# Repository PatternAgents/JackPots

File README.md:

# JackPots { ERA : Four (4) Attenuator, Eight (8) Jack board }

Format : ERA / Eurorack / Breadboard Friendly

Height : 1U 

Width: 16HP

Depth : 1.0 cm

Power : +12V 20mA

Jacks : 3.5mm mono (Thonkicon)

JackPots is a simple quad Attenuator I/O module.

[JackPots](https://github.com/patternagents/JackPots)

JackPots can be used on a breadboard for prototyping new circuits,
or it can mounted into a 1U Rack system using the following 1U x 16 HP front panel design.

[JackPots 1U Front Panel](https://github.com/patternagents/JackPots)

JackPots can be used in combination with two (2) or more other ERA modules
for mounting in a 3U ERA or Eurorack format card or even larger rack format

---------------------------------------

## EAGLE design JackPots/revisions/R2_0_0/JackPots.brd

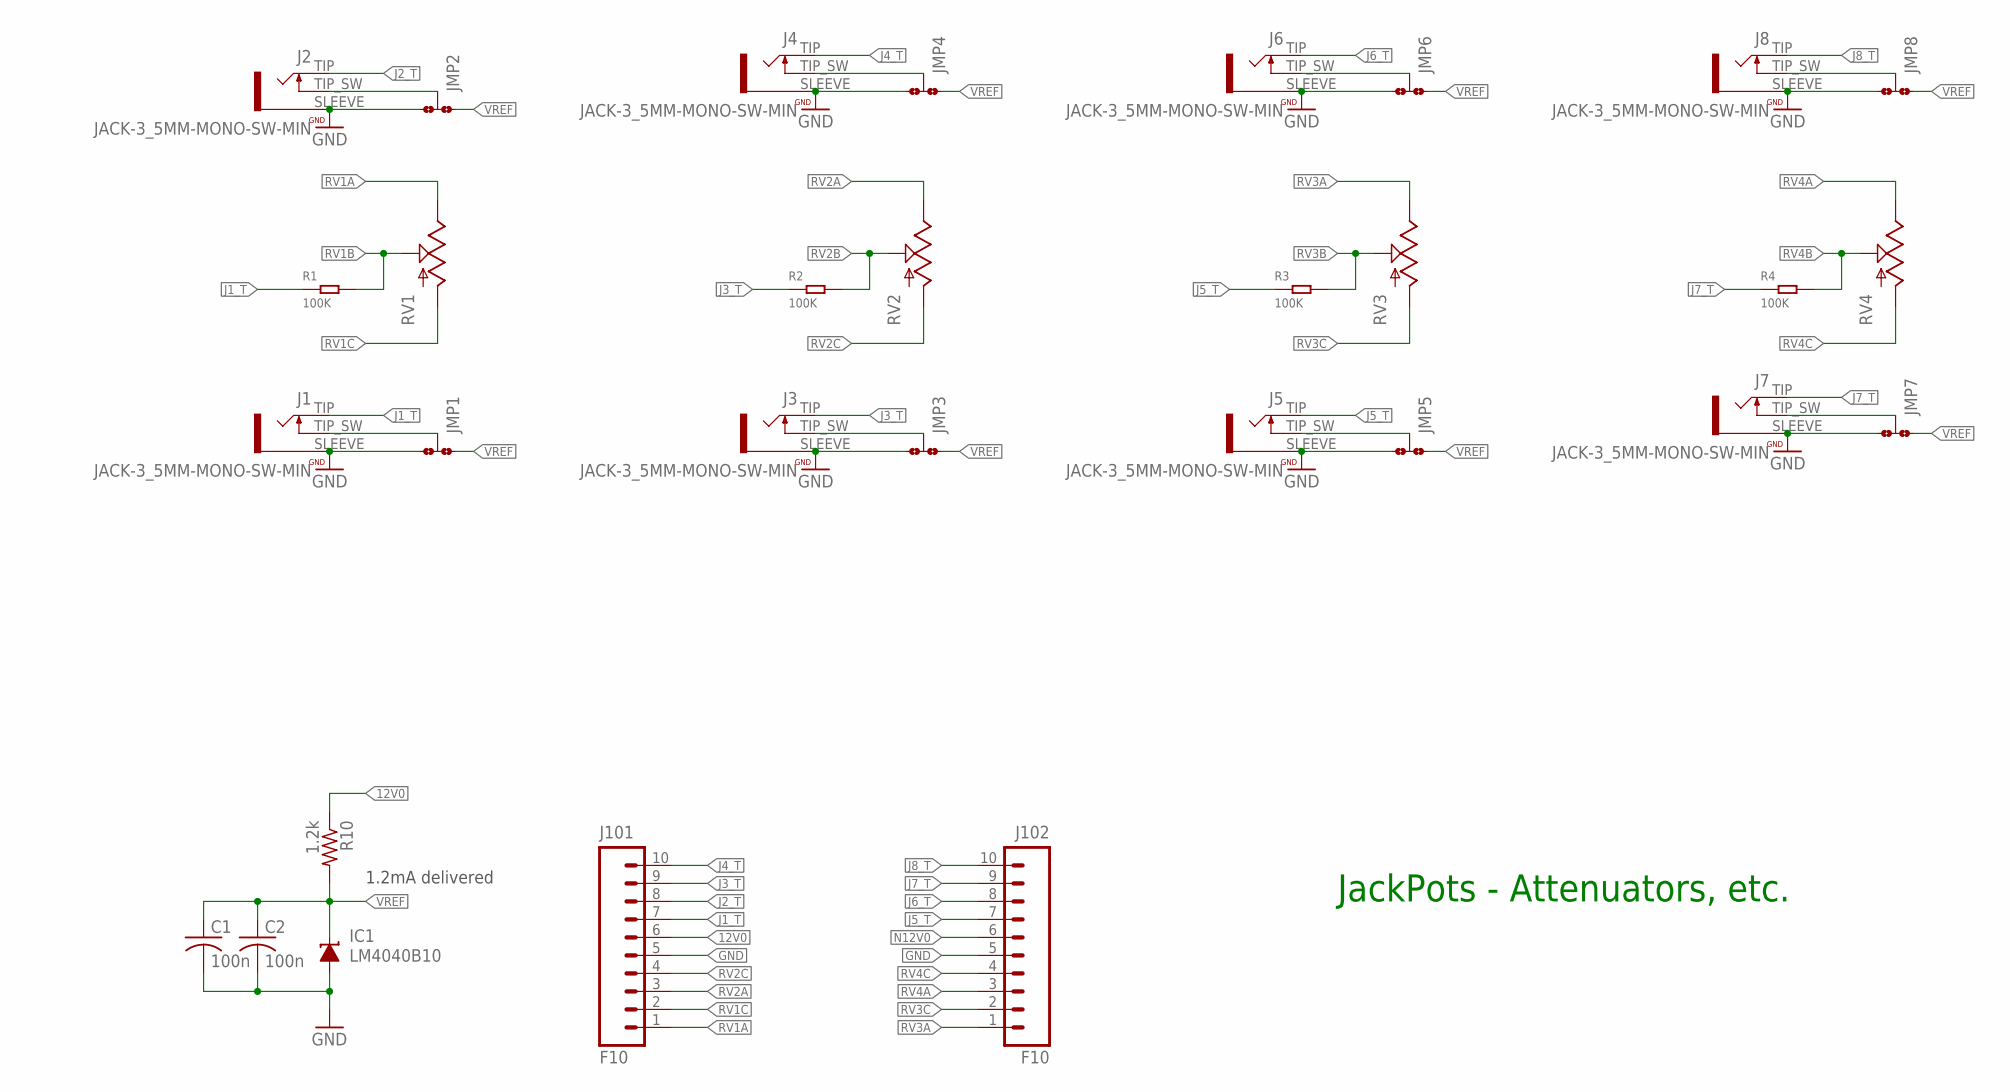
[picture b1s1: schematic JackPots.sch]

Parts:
C1, C2: 100n; C0603
IC1: LM4040B10; DBZ_R-PDSO-G3
J1, J2, J3, J4, J5, J6, J7, J8: JACK-3_5MM-MONO-SW-MIN; WQP_PJ301M-MIN
J101, J102: F10; 1X10_OCTO
JMP1, JMP2, JMP3, JMP4, JMP5, JMP6, JMP7, JMP8: JMP-3-NO-0603
R1, R2, R3, R4: 100K; R0603
R10: 1.2k; R0603
RV1, RV2, RV3, RV4: POT; ALPS_POT

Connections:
12V0: J101.6, R10.1
GND: C1.2, C2.2, IC1.2 (A), J1.SLEEVE, J2.SLEEVE, J3.SLEEVE, J4.SLEEVE, J5.SLEEVE, J6.SLEEVE, J7.SLEEVE, J8.SLEEVE, J101.5, J102.5, JMP1.3, JMP2.3, JMP3.3, JMP4.3, JMP5.3, JMP6.3, JMP7.3, JMP8.3
J1_T: J1.TIP, J101.7, R1.1
J1_TN: J1.TIP_SW, JMP1.2
J2_T: J2.TIP, J101.8
J2_TN: J2.TIP_SW, JMP2.2
J3_T: J3.TIP, J101.9, R2.1
J3_TN: J3.TIP_SW, JMP3.2
J4_T: J4.TIP, J101.10
J4_TN: J4.TIP_SW, JMP4.2
J5_T: J5.TIP, J102.7, R3.1
J5_TN: J5.TIP_SW, JMP5.2
J6_T: J6.TIP, J102.8
J6_TN: J6.TIP_SW, JMP6.2
J7_T: J7.TIP, J102.9, R4.1
J7_TN: J7.TIP_SW, JMP7.2
J8_T: J8.TIP, J102.10
J8_TN: J8.TIP_SW, JMP8.2
N12V0: J102.6
RV1A: J101.1, RV1.P$1 (3)
RV1B: R1.2, RV1.P$2 (2)
RV1C: J101.2, RV1.P$3 (1)
RV2A: J101.3, RV2.P$1 (3)
RV2B: R2.2, RV2.P$2 (2)
RV2C: J101.4, RV2.P$3 (1)
RV3A: J102.1, RV3.P$1 (3)
RV3B: R3.2, RV3.P$2 (2)
RV3C: J102.2, RV3.P$3 (1)
RV4A: J102.3, RV4.P$1 (3)
RV4B: R4.2, RV4.P$2 (2)
RV4C: J102.4, RV4.P$3 (1)
VREF: C1.1, C2.1, IC1.1 (C), JMP1.1, JMP2.1, JMP3.1, JMP4.1, JMP5.1, JMP6.1, JMP7.1, JMP8.1, R10.2

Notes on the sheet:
JackPots - Attenuators, etc.
1.2mA delivered

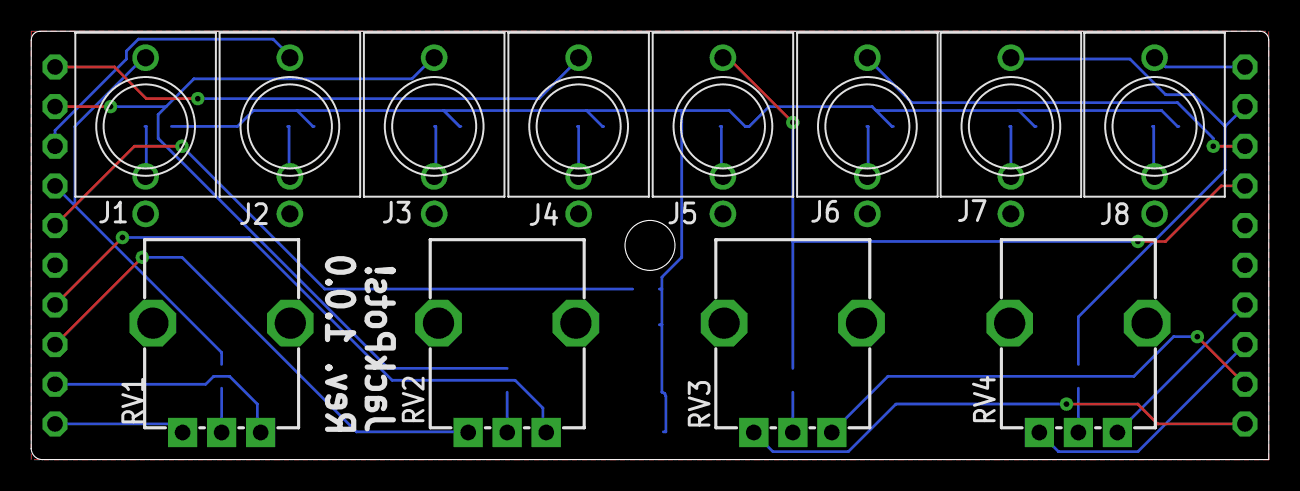
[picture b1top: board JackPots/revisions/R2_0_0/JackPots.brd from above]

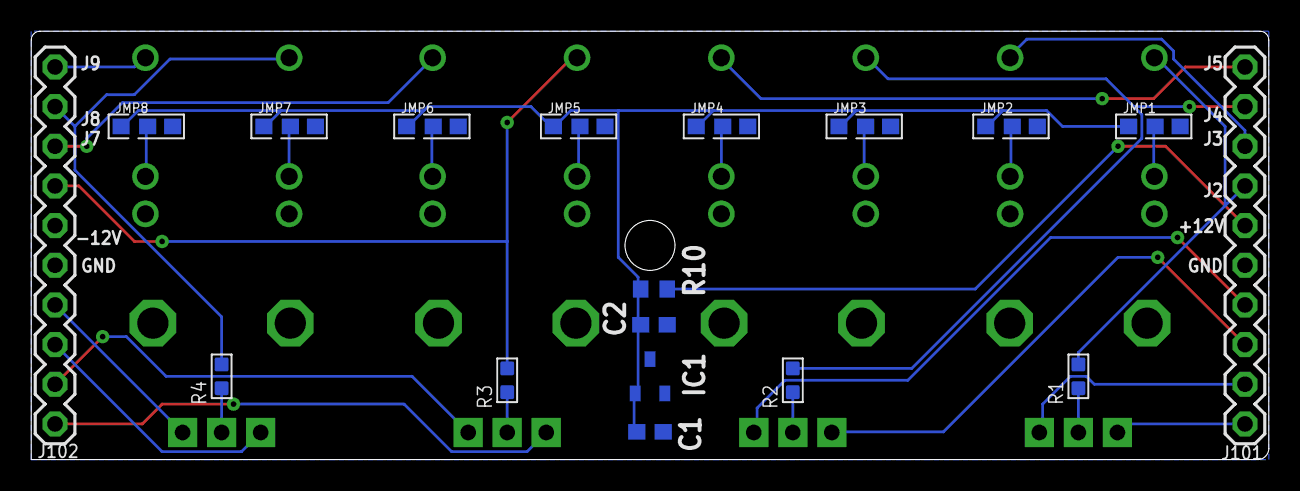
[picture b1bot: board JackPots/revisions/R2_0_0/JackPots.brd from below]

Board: 2 copper layers, 79.2 x 27.4 mm, 30 parts (18 on the bottom side), 31 nets.

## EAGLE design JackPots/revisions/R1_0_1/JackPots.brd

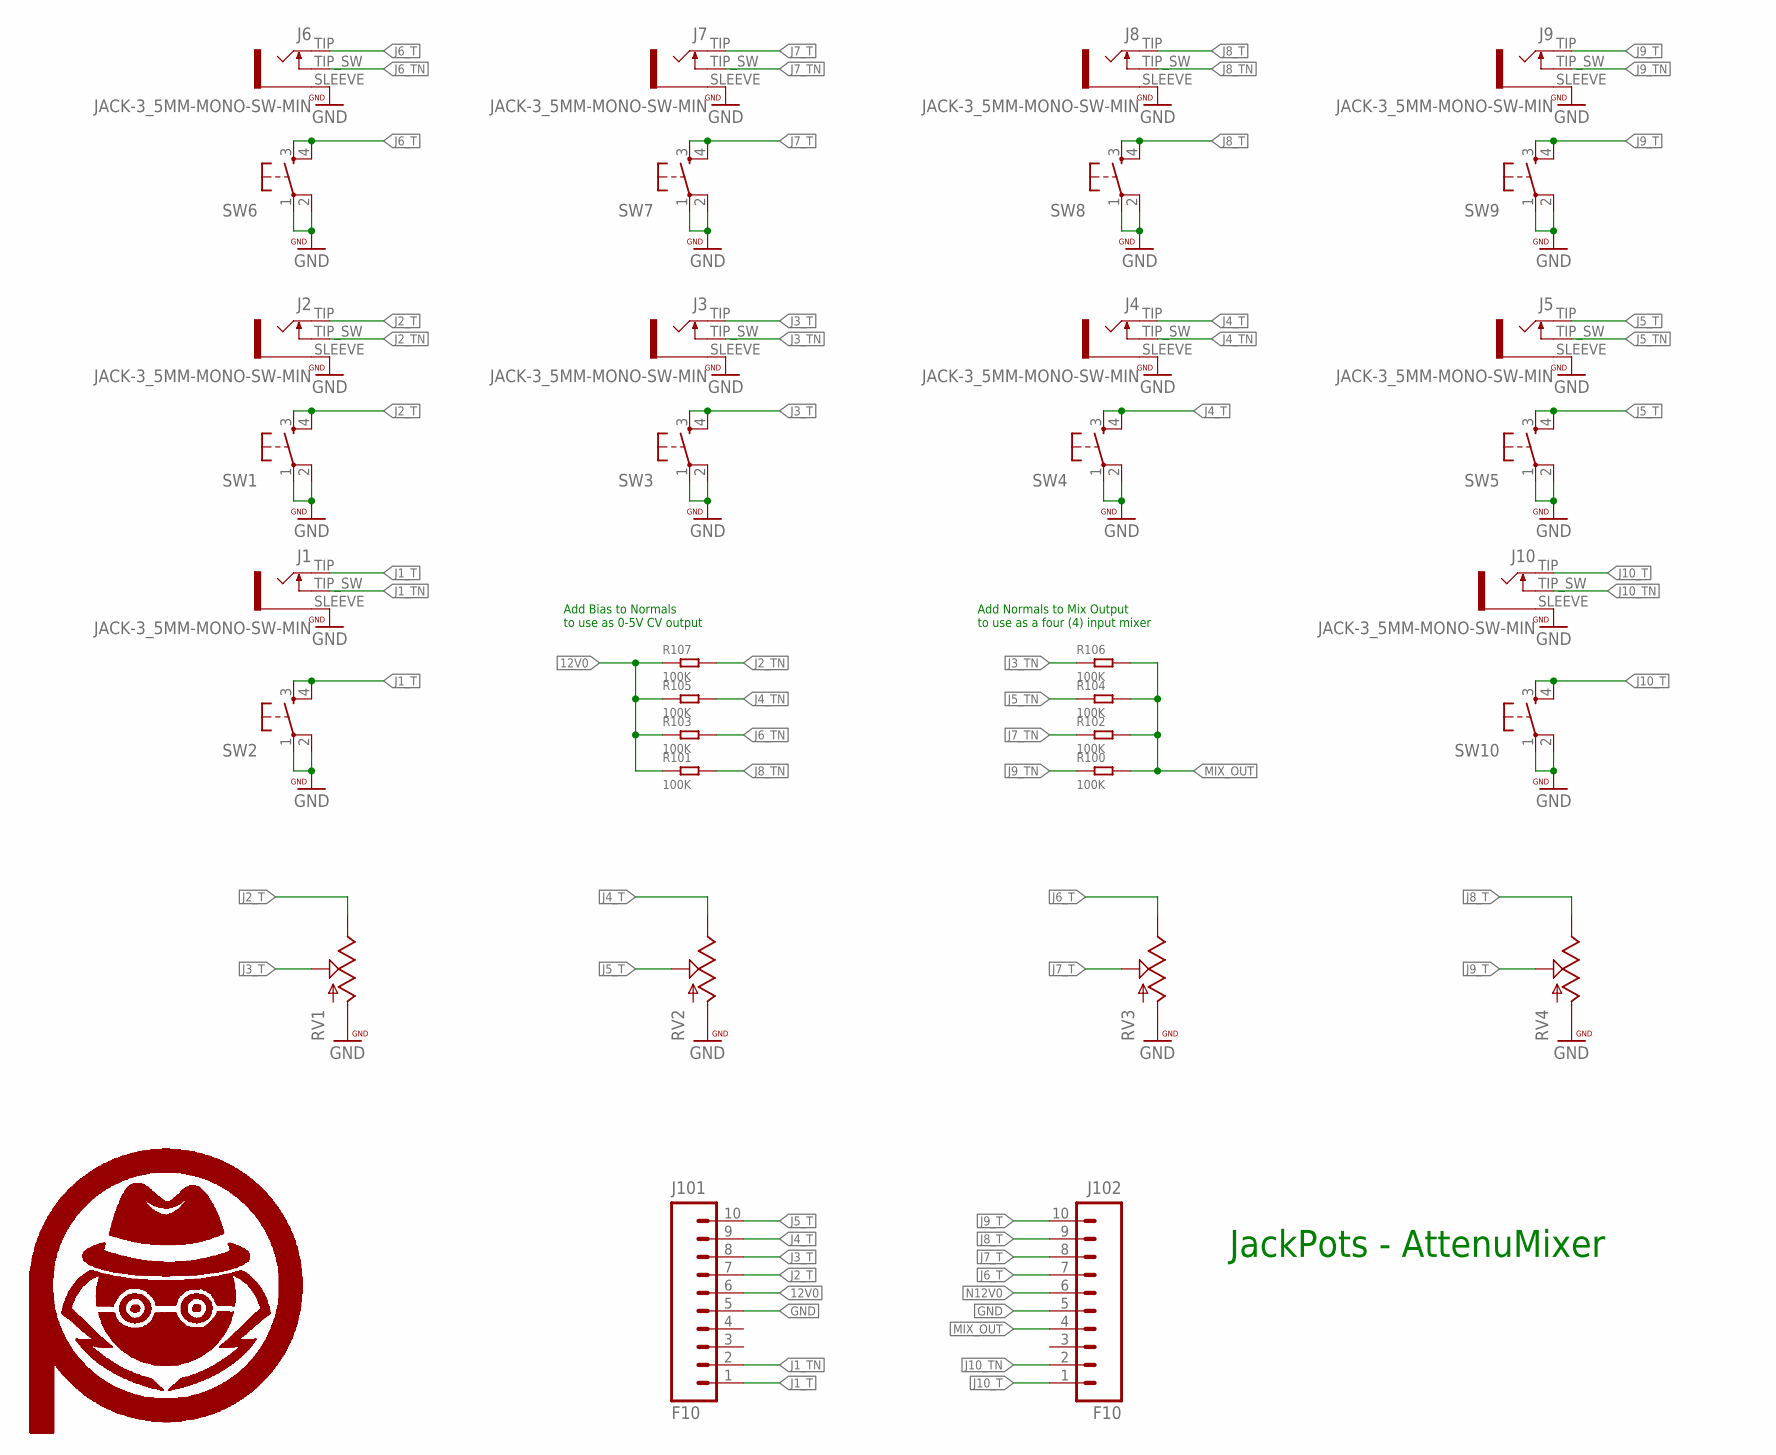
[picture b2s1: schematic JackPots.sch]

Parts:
$$U$1: PA_LOGO_SYMSMALL; PA_LOGO_AGENT_SMALL_SYM
$$U$100, $$U$101: PA_LOGO_SYMMED; PA_LOGO_AGENT_MED_SYM
J1, J2, J3, J4, J5, J6, J7, J8, J9, J10: JACK-3_5MM-MONO-SW-MIN; WQP_PJ301M-MIN
J101, J102: F10; 1X10_OCTO
R100, R101, R102, R103, R104, R105, R106, R107: 100K; R0603
RV1, RV2, RV3, RV4: POT; ALPS_POT
SW1, SW2, SW3, SW4, SW5, SW6, SW7, SW8, SW9, SW10: TAC_SWITCHPTH; TACTILE-PTH

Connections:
12V0: J101.6, R101.1, R103.1, R105.1, R107.1
GND: J1.SLEEVE, J2.SLEEVE, J3.SLEEVE, J4.SLEEVE, J5.SLEEVE, J6.SLEEVE, J7.SLEEVE, J8.SLEEVE, J9.SLEEVE, J10.SLEEVE, J101.5, J102.5, RV1.P$3 (1), RV2.P$3 (1), RV3.P$3 (1), RV4.P$3 (1), SW1.1, SW1.2, SW2.1, SW2.2, SW3.1, SW3.2, SW4.1, SW4.2, SW5.1, SW5.2, SW6.1, SW6.2, SW7.1, SW7.2, SW8.1, SW8.2, SW9.1, SW9.2, SW10.1, SW10.2
J1_T: J1.TIP, J101.1, SW2.3, SW2.4
J1_TN: J1.TIP_SW, J101.2
J2_T: J2.TIP, J101.7, RV1.P$1 (3), SW1.3, SW1.4
J2_TN: J2.TIP_SW, R107.2
J3_T: J3.TIP, J101.8, RV1.P$2 (2), SW3.3, SW3.4
J3_TN: J3.TIP_SW, R106.1
J4_T: J4.TIP, J101.9, RV2.P$1 (3), SW4.3, SW4.4
J4_TN: J4.TIP_SW, R105.2
J5_T: J5.TIP, J101.10, RV2.P$2 (2), SW5.3, SW5.4
J5_TN: J5.TIP_SW, R104.1
J6_T: J6.TIP, J102.7, RV3.P$1 (3), SW6.3, SW6.4
J6_TN: J6.TIP_SW, R103.2
J7_T: J7.TIP, J102.8, RV3.P$2 (2), SW7.3, SW7.4
J7_TN: J7.TIP_SW, R102.1
J8_T: J8.TIP, J102.9, RV4.P$1 (3), SW8.3, SW8.4
J8_TN: J8.TIP_SW, R101.2
J9_T: J9.TIP, J102.10, RV4.P$2 (2), SW9.3, SW9.4
J9_TN: J9.TIP_SW, R100.1
J10_T: J10.TIP, J102.1, SW10.3, SW10.4
J10_TN: J10.TIP_SW, J102.2
MIX_OUT: J102.4, R100.2, R102.2, R104.2, R106.2
N12V0: J102.6

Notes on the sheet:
Add Bias to Normals to use as 0-5V CV output
Add Normals to Mix Output to use as a four (4) input mixer
JackPots - AttenuMixer

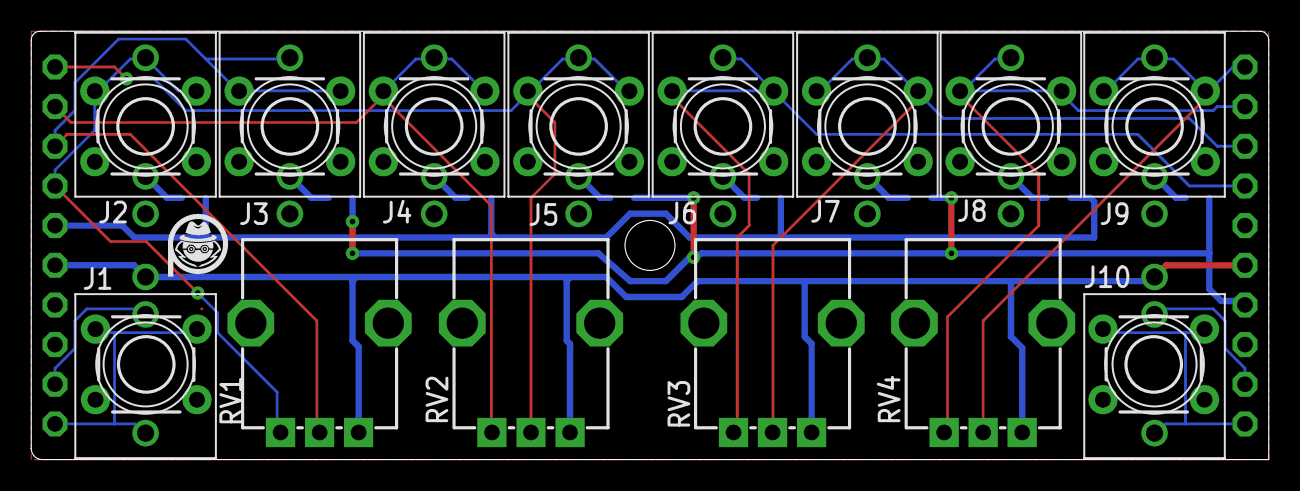
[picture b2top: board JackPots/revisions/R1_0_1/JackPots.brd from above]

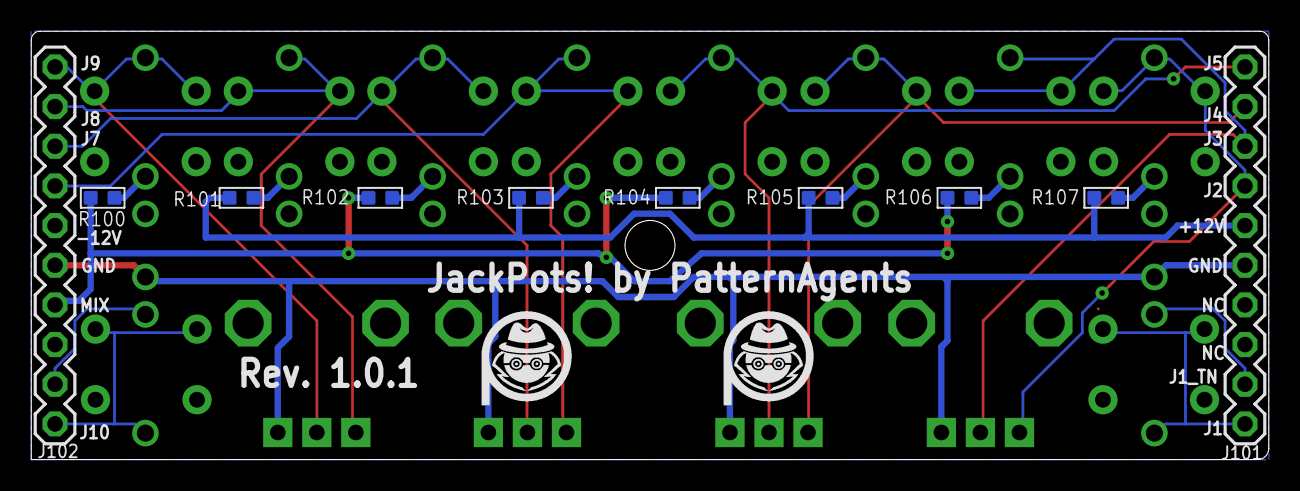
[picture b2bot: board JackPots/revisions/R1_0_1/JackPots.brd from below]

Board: 2 copper layers, 79.2 x 27.4 mm, 37 parts (12 on the bottom side), 23 nets.

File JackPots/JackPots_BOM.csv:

"Qty";"Value";"Device";"Package";"Parts";"Description";"";
"4";"";"POT";"ALPS_POT";"RV1, RV2, RV3, RV4";"";"";
"10";"";"TAC_SWITCHPTH";"TACTILE-PTH";"SW1, SW2, SW3, SW4, SW5, SW6, SW7, SW8, SW9, SW10";"Momentary Switch";"";
"8";"100K";"SMD-RES-100K-1%-1/10W(0603)";"R0603";"R100, R101, R102, R103, R104, R105, R106, R107";"301010196";"";
"2";"F10";"M10SILK_FEMALE_PTH";"1X10_OCTO";"J101, J102";"Header 10";"";
"10";"JACK-3_5MM-MONO-SW-MIN";"JACK-3_5MM-MONO-SW-MIN";"WQP_PJ301M-MIN";"J1, J2, J3, J4, J5, J6, J7, J8, J9, J10";"Jack, 3.5mm, RIght Angle, Though-Hole";"";
"2";"PA_LOGO_SYMMED";"PA_LOGO_SYMMED";"PA_LOGO_AGENT_MED_SYM";"$$U$100, $$U$101";"PatternAgents Logo Symbol";"";
"1";"PA_LOGO_SYMSMALL";"PA_LOGO_SYMSMALL";"PA_LOGO_AGENT_SMALL_SYM";"$$U$1";"PatternAgents Logo Symbol";"";

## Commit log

2018-01-21 initial version
2018-04-10 4/10 update
2018-04-17 update for more space between pots, etc.

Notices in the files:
README.md:
License: CC BY-NC 4.0
parts and their libraries:
PatternAgents-Beautify: License : http://creativecommons.org/licenses/by-sa/3.0
(Creative Commons 3.0)
PatternAgents-ProtoPads: License : http://creativecommons.org/licenses/by-sa/4.0
(Creative Commons 4.0)
